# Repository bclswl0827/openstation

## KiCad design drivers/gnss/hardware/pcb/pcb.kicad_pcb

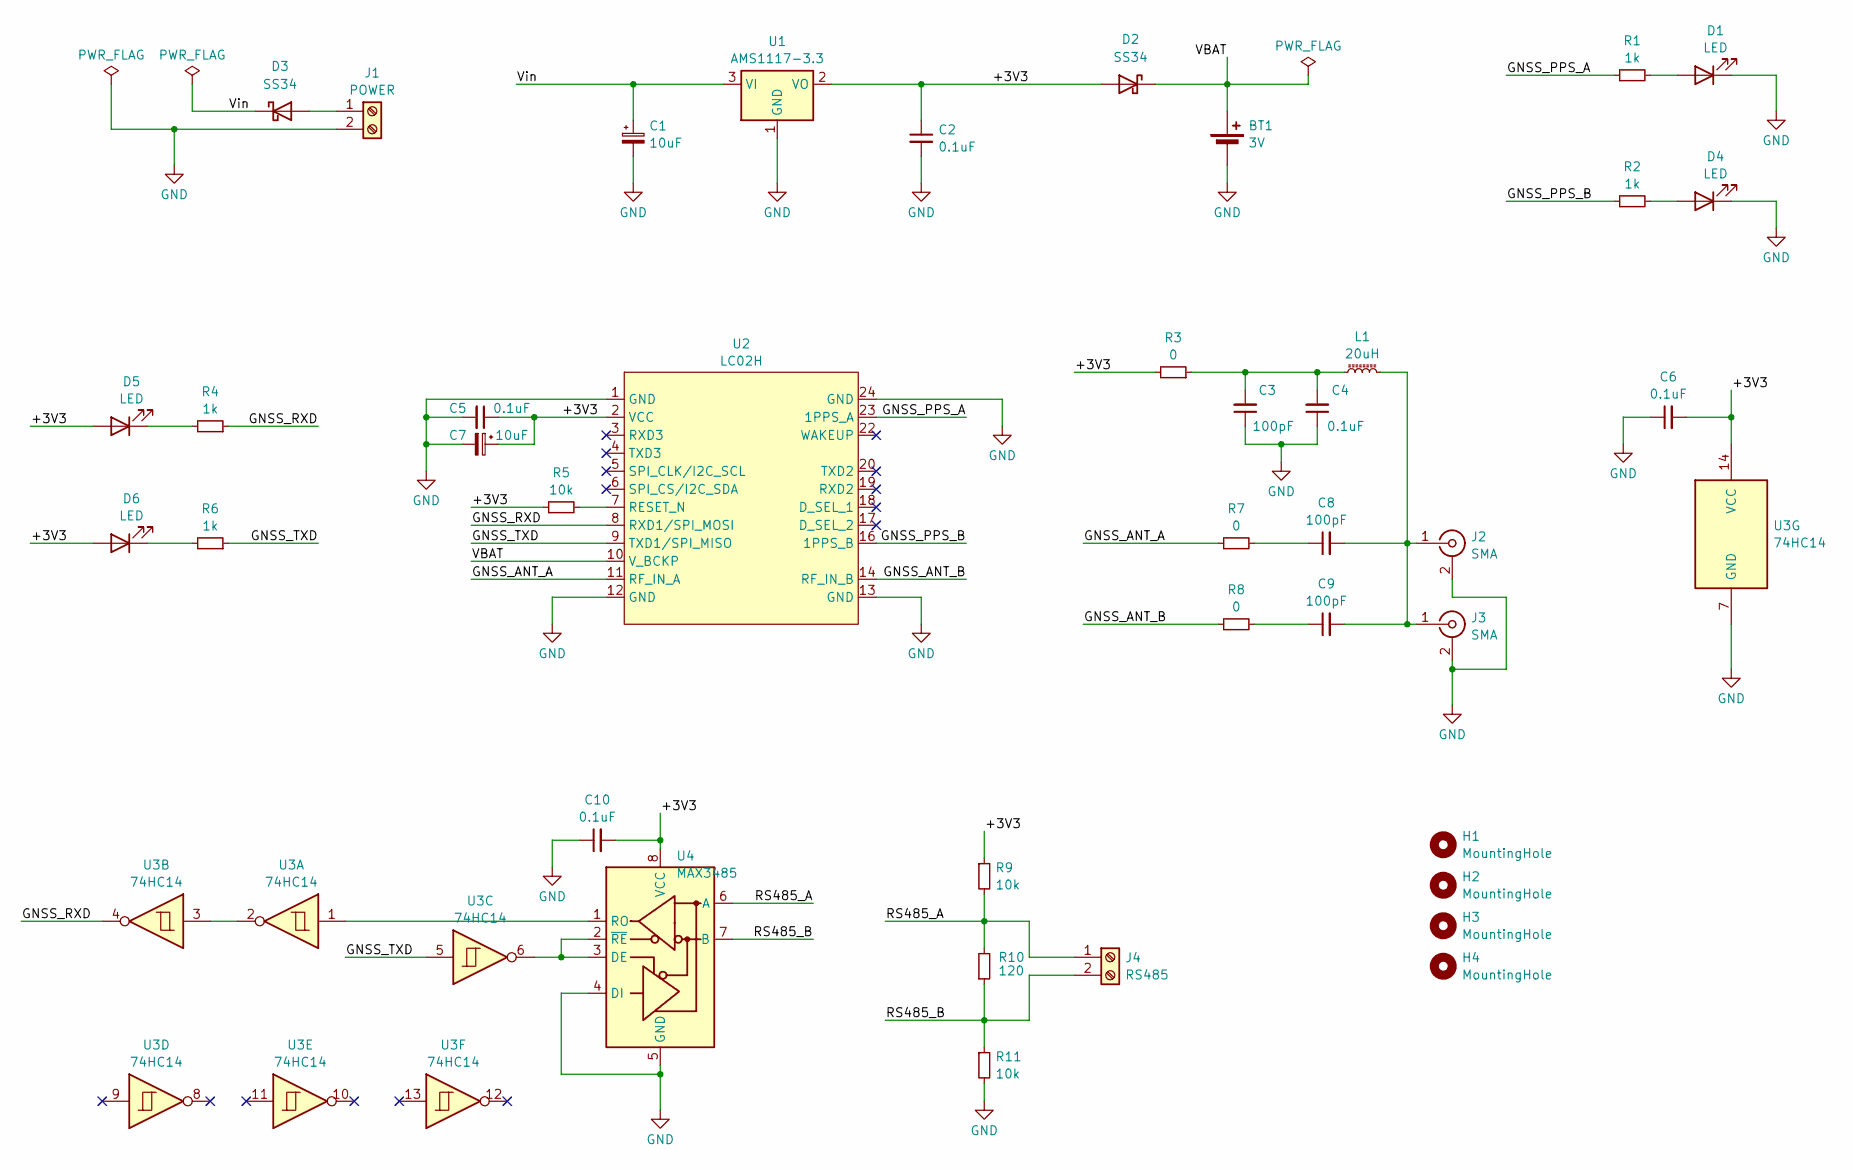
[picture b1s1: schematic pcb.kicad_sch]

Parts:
BT1: 3V; BatteryHolder_LINX_BAT-HLD-012-SMT
C1, C7: 10uF; CP_Radial_D5.0mm_P2.50mm
C2, C4, C5, C6, C10: 0.1uF; C_Disc_D3.0mm_W2.0mm_P2.50mm
C3, C8, C9: 100pF; C_Disc_D3.0mm_W2.0mm_P2.50mm
D1, D4, D5, D6: LED; LED_D3.0mm
D2, D3: SS34; D_SMA
H1, H2, H3, H4: MountingHole; MountingHole_3.2mm_M3_DIN965
J1: POWER; TerminalBlock_bornier-2_P5.08mm
J2, J3: SMA; SMA_Amphenol_901-144_Vertical
J4: RS485; TerminalBlock_bornier-2_P5.08mm
L1: 20uH; L_Radial_D7.0mm_P3.00mm
R1, R2, R4, R6: 1k; R_Axial_DIN0204_L3.6mm_D1.6mm_P7.62mm_Horizontal
R3, R7, R8: 0; R_Axial_DIN0204_L3.6mm_D1.6mm_P7.62mm_Horizontal
R5, R9, R11: 10k; R_Axial_DIN0204_L3.6mm_D1.6mm_P7.62mm_Horizontal
R10: 120; R_Axial_DIN0204_L3.6mm_D1.6mm_P7.62mm_Horizontal
U1: AMS1117-3.3; SOT-223-3_TabPin2
U2: LC02H
U3: 74HC14; SOIC-14_3.9x8.7mm_P1.27mm
U4: MAX3485; SOIC-8_3.9x4.9mm_P1.27mm

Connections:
/+3V3: C2.1, C5.1, C6.2, C7.1, C10.2, D2.2 (A), D5.2 (A), D6.2 (A), R3.2, R5.1, R9.1, U1.2 (VO), U2.2 (VCC), U3.14 (VCC), U4.8 (VCC)
/GNSS_ANT_A: R7.1, U2.11 (RF_IN_A)
/GNSS_ANT_B: R8.1, U2.14 (RF_IN_B)
/GNSS_PPS_A: R1.1, U2.23 (1PPS_A)
/GNSS_PPS_B: R2.1, U2.16 (1PPS_B)
/GNSS_RXD: R4.1, U2.8 (RXD1/SPI_MOSI), U3.4
/GNSS_TXD: R6.1, U2.9 (TXD1/SPI_MISO), U3.5
/RS485_A: J4.1, R9.2, R10.2, U4.6 (A)
/RS485_B: J4.2, R10.1, R11.1, U4.7 (B)
/VBAT: BT1.1 (+), D2.1 (K), U2.10 (V_BCKP)
/Vin: C1.1, D3.1 (K), U1.3 (VI)
GND: BT1.2 (-), C1.2, C2.2, C3.1, C4.1, C5.2, C6.1, C7.2, C10.1, D1.1 (K), D4.1 (K), J1.2, J2.2 (Ext), J3.2 (Ext), R11.2, U1.1 (GND), U2.1 (GND), U2.12 (GND), U2.13 (GND), U2.24 (GND), U3.7 (GND), U4.4 (DI), U4.5 (GND)
unnamed: C3.2, C4.2, L1.1, R3.1
unnamed: C8.1, R7.2
unnamed: C9.1, R8.2
unnamed: D1.2 (A), R1.2
unnamed: D3.2 (A), J1.1
unnamed: D4.2 (A), R2.2
unnamed: D5.1 (K), R4.2
unnamed: D6.1 (K), R6.2
unnamed: C8.2, C9.2, J2.1 (In), J3.1 (In), L1.2
unnamed: R5.2, U2.7 (RESET_N)
unnamed: U3.2, U3.3
unnamed: U3.6, U4.2 (~RE), U4.3 (DE)
unnamed: U3.1, U4.1 (RO)

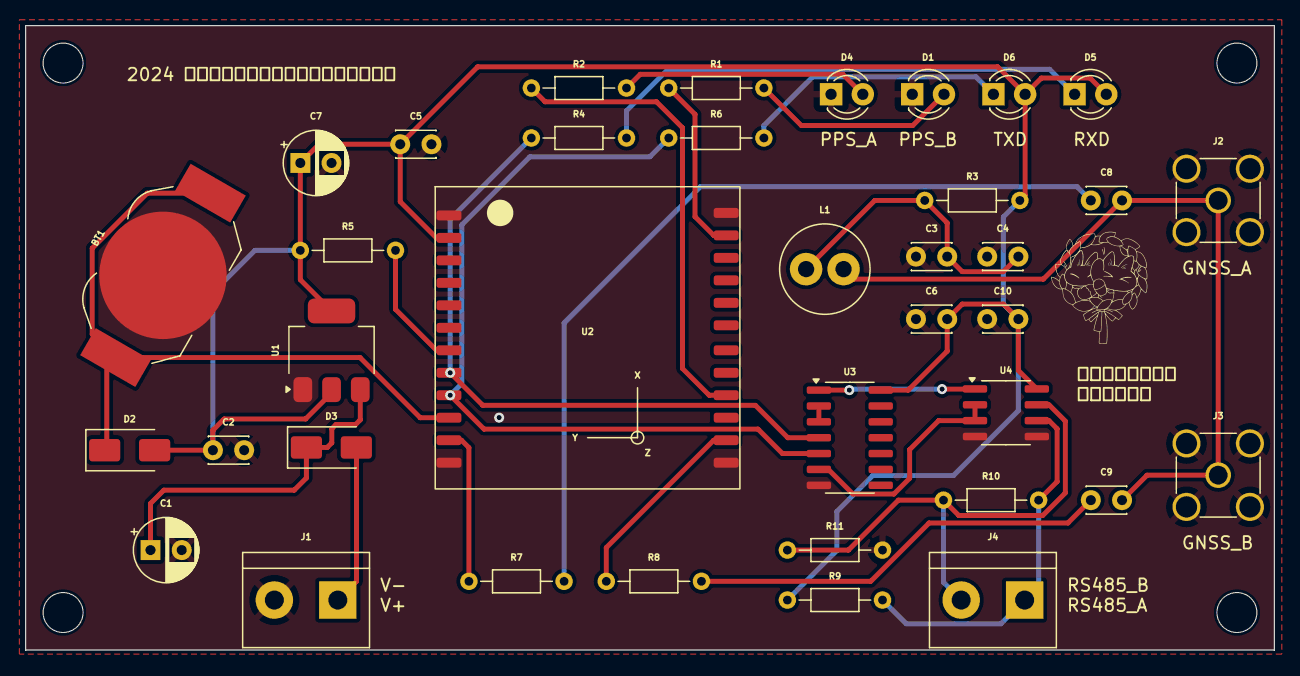
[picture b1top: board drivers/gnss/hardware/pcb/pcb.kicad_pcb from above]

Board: 2 copper layers, 100.0 x 50.0 mm, 41 parts (0 on the bottom side), 25 nets.

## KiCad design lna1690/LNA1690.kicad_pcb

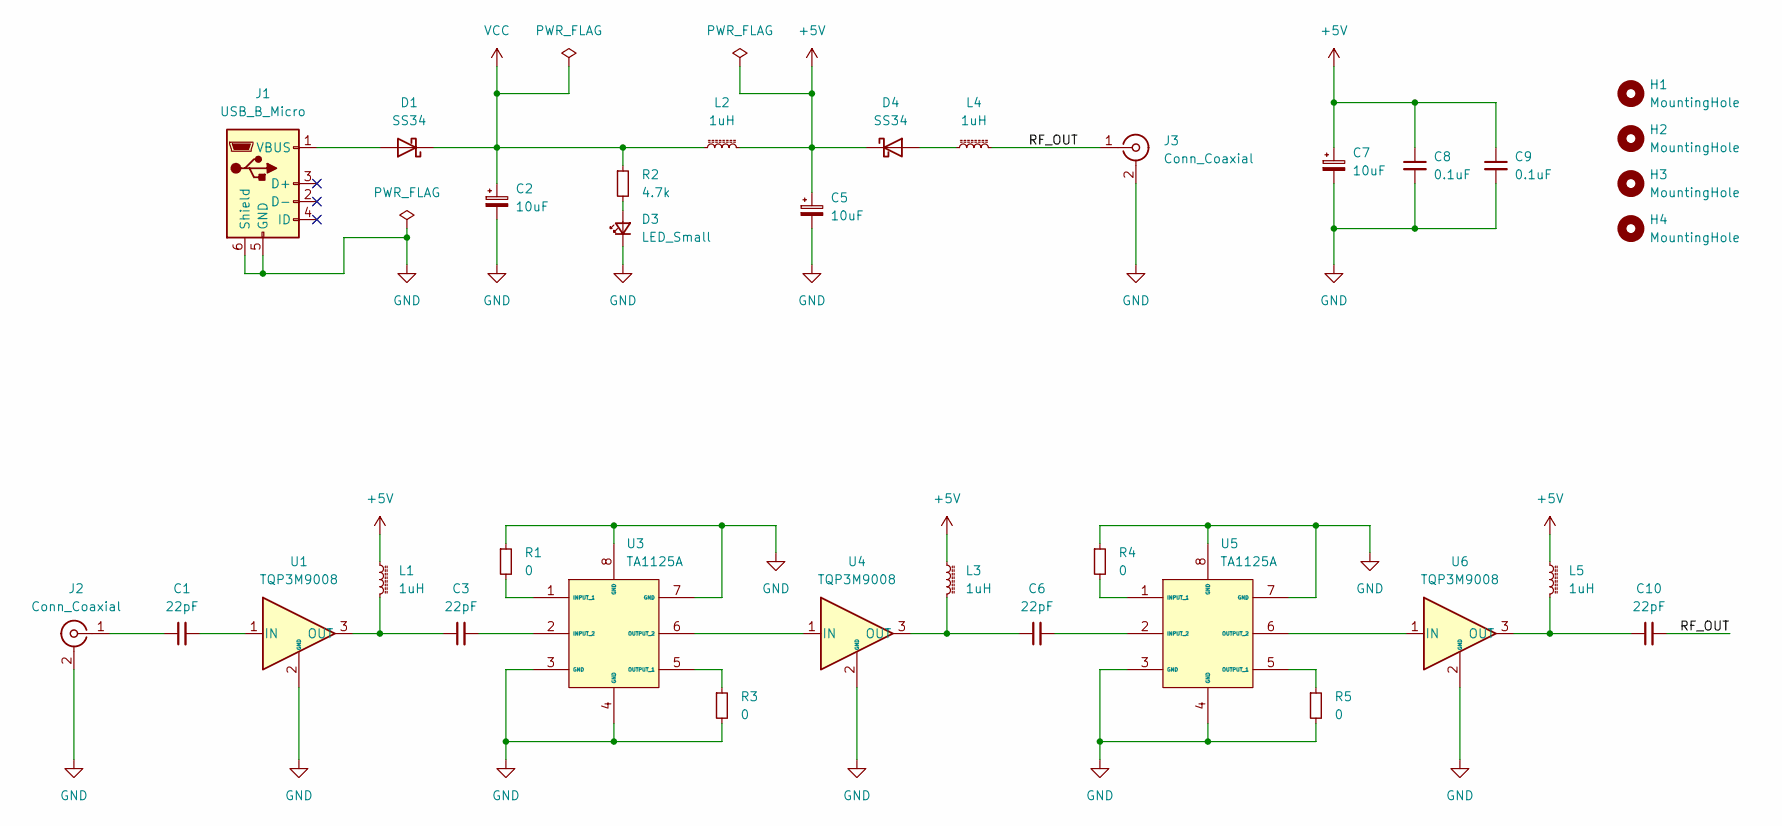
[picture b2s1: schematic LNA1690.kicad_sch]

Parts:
C1, C3, C6, C10: 22pF; C_0603_1608Metric
C2, C5, C7: 10uF; CP_EIA-3528-12_Kemet-T
C8, C9: 0.1uF; C_0603_1608Metric
D1, D4: SS34; D_SMA
D3: LED_Small; LED_0603_1608Metric
H1, H2, H3, H4: MountingHole; MountingHole_3.2mm_M3
J1: USB_B_Micro; USB_Micro-B_Amphenol_10103594-0001LF_Horizontal
J2, J3: Conn_Coaxial; SMA_Amphenol_901-144_Vertical
L1, L2, L3, L4, L5: 1uH; L_0603_1608Metric
R1, R3, R4, R5: 0; R_0603_1608Metric
R2: 4.7k; R_0603_1608Metric
U1, U4, U6: TQP3M9008; SOT-89-3
U3, U5: TA1125A; Filter_SAW-8_3.8x3.8mm

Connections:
+5V: C5.1, C7.1, C8.1, C9.1, D4.1 (K), L1.1, L2.2, L3.1, L5.1
/RF_OUT: C10.2, J3.1 (In), L4.2
GND: C2.2, C5.2, C7.2, C8.2, C9.2, D3.1 (K), J1.5 (GND), J1.6 (Shield), J2.2 (Ext), J3.2 (Ext), R1.1, R3.2, R4.1, R5.2, U1.2 (GND), U3.3 (GND), U3.4 (GND), U3.7 (GND), U3.8 (GND), U4.2 (GND), U5.3 (GND), U5.4 (GND), U5.7 (GND), U5.8 (GND), U6.2 (GND)
unnamed: D1.2 (A), J1.1 (VBUS)
unnamed: D3.2 (A), R2.2
unnamed: D4.2 (A), L4.1
unnamed: C1.1, J2.1 (In)
unnamed: C1.2, U1.1 (IN)
unnamed: C3.1, L1.2, U1.3 (OUT)
unnamed: R1.2, U3.1 (INPUT_1)
unnamed: C3.2, U3.2 (INPUT_2)
unnamed: R3.1, U3.5 (OUTPUT_1)
unnamed: U3.6 (OUTPUT_2), U4.1 (IN)
unnamed: C6.1, L3.2, U4.3 (OUT)
unnamed: R4.2, U5.1 (INPUT_1)
unnamed: C6.2, U5.2 (INPUT_2)
unnamed: R5.1, U5.5 (OUTPUT_1)
unnamed: U5.6 (OUTPUT_2), U6.1 (IN)
unnamed: C10.1, L5.2, U6.3 (OUT)
VCC: C2.1, D1.1 (K), L2.1, R2.1

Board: 2 copper layers, 34 parts (0 on the bottom side), 20 nets, no tracks yet.

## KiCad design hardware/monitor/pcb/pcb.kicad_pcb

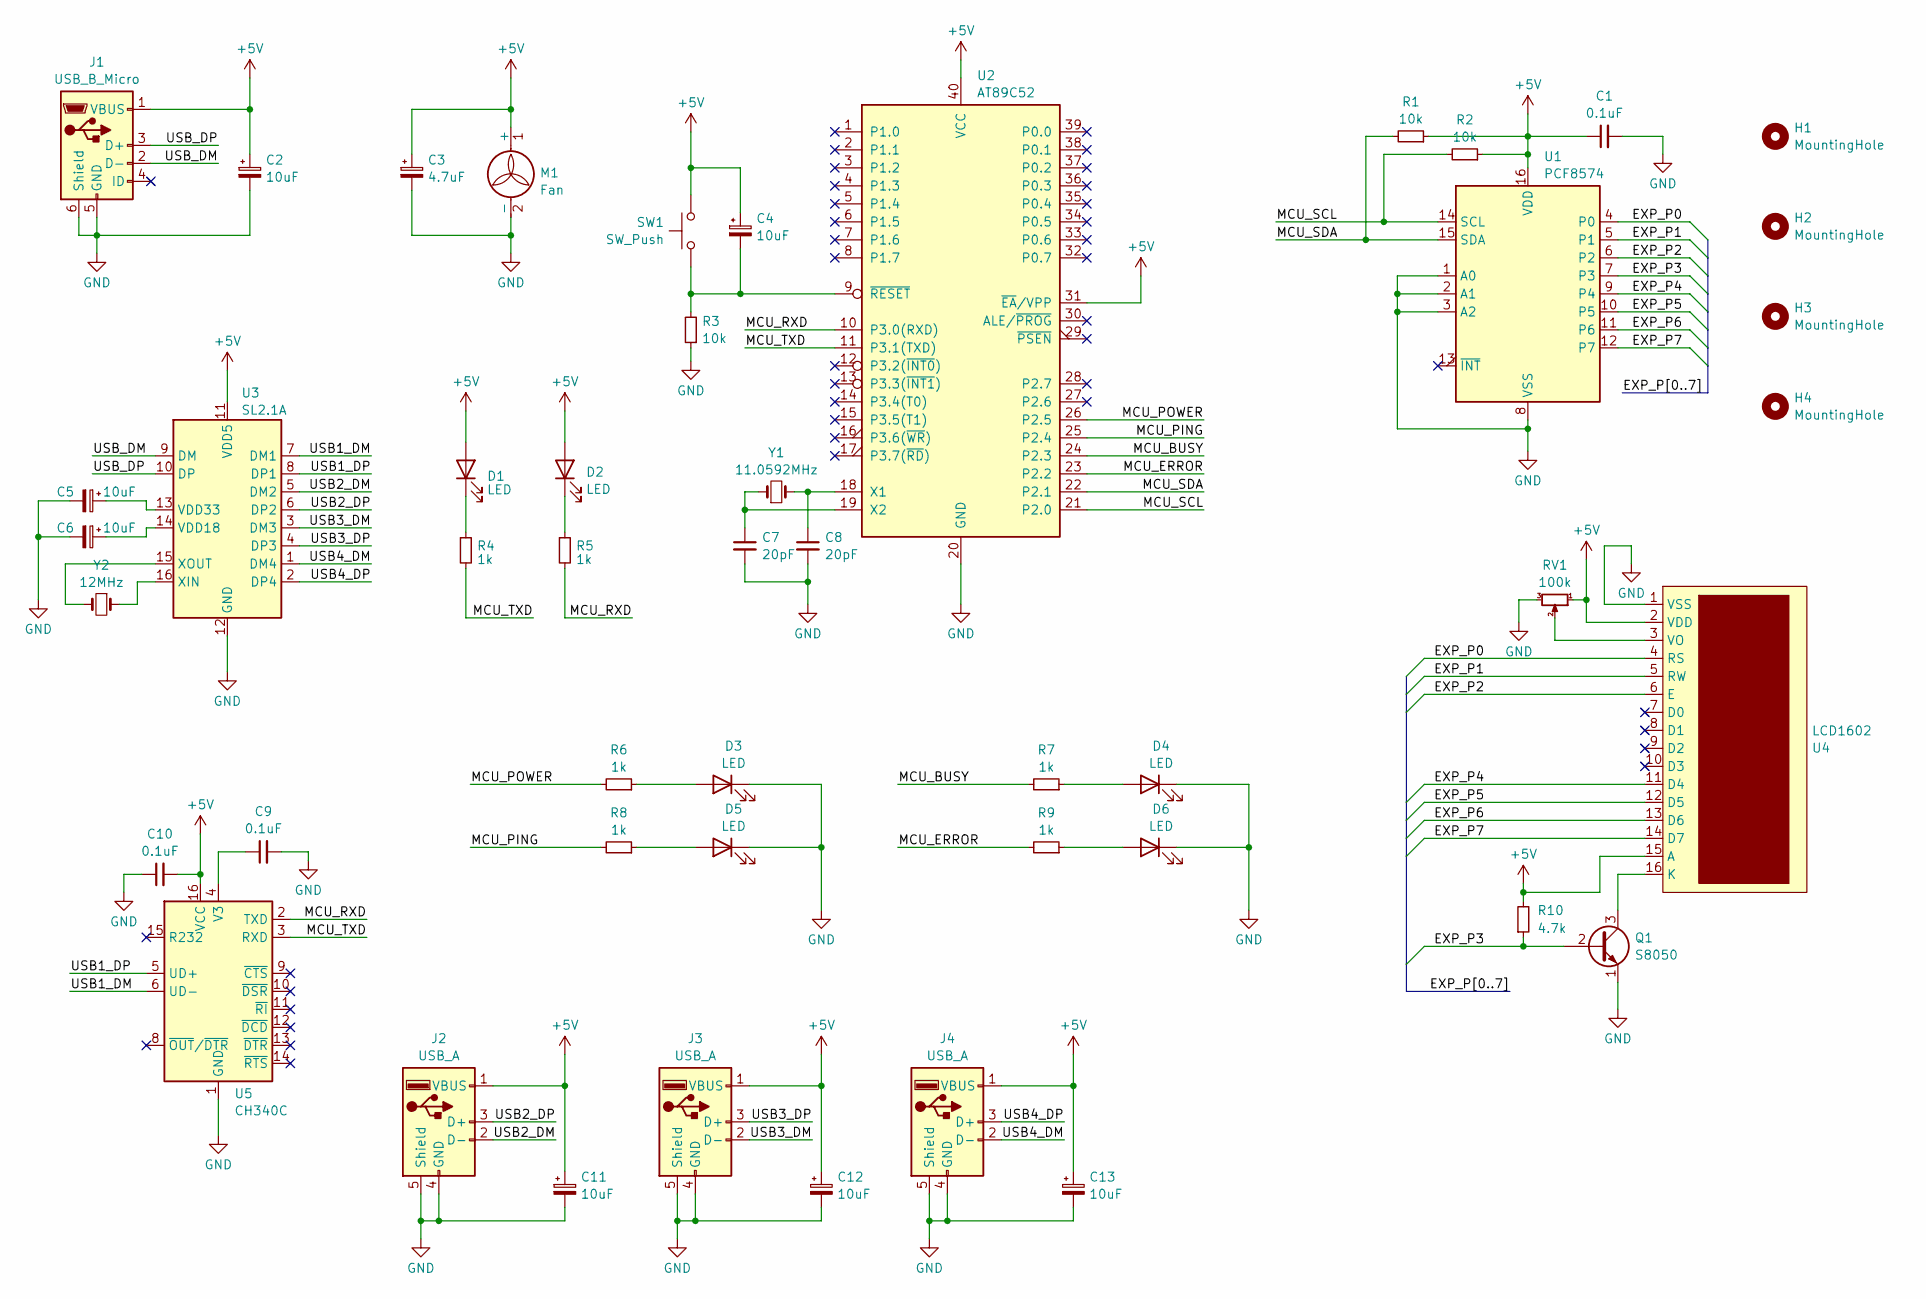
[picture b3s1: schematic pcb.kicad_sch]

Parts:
C1, C9, C10: 0.1uF; C_Disc_D3.0mm_W2.0mm_P2.50mm
C2, C4, C5, C6, C11, C12, C13: 10uF; CP_Radial_D5.0mm_P2.50mm
C3: 4.7uF; CP_Radial_D5.0mm_P2.50mm
C7, C8: 20pF; C_Disc_D3.0mm_W2.0mm_P2.50mm
D1, D2, D3, D4, D5, D6: LED; LED_D3.0mm
H1, H2, H3, H4: MountingHole; MountingHole_3.2mm_M3
J1: USB_B_Micro; USB_Micro-B_Molex-105017-0001
J2, J3, J4: USB_A; USB_A_CONNFLY_DS1095-WNR0
M1: Fan; Fan_30x30mm
Q1: S8050; TO-92_Inline
R1, R2, R3: 10k; R_Axial_DIN0204_L3.6mm_D1.6mm_P7.62mm_Horizontal
R4, R5, R6, R7, R8, R9: 1k; R_Axial_DIN0204_L3.6mm_D1.6mm_P7.62mm_Horizontal
R10: 4.7k; R_Axial_DIN0204_L3.6mm_D1.6mm_P7.62mm_Horizontal
RV1: 100k; Potentiometer_Bourns_3296W_Vertical
SW1: SW_Push; SW_SPST_FSMSM
U1: PCF8574; SOIC-16W_7.5x10.3mm_P1.27mm
U2: AT89C52; DIP-40_W15.24mm
U3: SL2.1A; SOIC-16_3.9x9.9mm_P1.27mm
U4: LCD1602
U5: CH340C; SOIC-16_3.9x9.9mm_P1.27mm
Y1: 11.0592MHz; Crystal_HC18-U_Vertical
Y2: 12MHz; Crystal_HC18-U_Vertical

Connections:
+5V: C1.1, C2.1, C3.1, C4.1, C10.2, C11.1, C12.1, C13.1, D1.2 (A), D2.2 (A), J1.1 (VBUS), J2.1 (VBUS), J3.1 (VBUS), J4.1 (VBUS), M1.1 (+), R1.1, R2.1, R10.2, RV1.1, SW1.1, U1.16 (VDD), U2.31 (~EA/VPP), U2.40 (VCC), U3.11 (VDD5), U4.2 (VDD), U4.15 (A), U5.16 (VCC); also elsewhere on the board
/EXP_P0: U1.4 (P0), U4.4 (RS)
/EXP_P1: U1.5 (P1), U4.5 (RW)
/EXP_P2: U1.6 (P2), U4.6 (E)
/EXP_P3: Q1.2 (B), R10.1, U1.7 (P3)
/EXP_P4: U1.9 (P4), U4.11 (D4)
/EXP_P5: U1.10 (P5), U4.12 (D5)
/EXP_P6: U1.11 (P6), U4.13 (D6)
/EXP_P7: U1.12 (P7), U4.14 (D7)
/MCU_BUSY: R7.2, U2.24 (P2.3)
/MCU_ERROR: R9.2, U2.23 (P2.2)
/MCU_PING: R8.2, U2.25 (P2.4)
/MCU_POWER: R6.2, U2.26 (P2.5)
/MCU_RXD: R5.2, U2.10 (P3.0(RXD)), U5.2 (TXD); also elsewhere on the board
/MCU_SCL: R2.2, U1.14 (SCL), U2.21 (P2.0)
/MCU_SDA: R1.2, U1.15 (SDA), U2.22 (P2.1)
/MCU_TXD: R4.2, U2.11 (P3.1(TXD)), U5.3 (RXD); also elsewhere on the board
/USB1_DM: U3.7 (DM1), U5.6 (UD-); also elsewhere on the board
/USB1_DP: U3.8 (DP1), U5.5 (UD+); also elsewhere on the board
/USB2_DM: J2.2 (D-), U3.5 (DM2)
/USB2_DP: J2.3 (D+), U3.6 (DP2)
/USB3_DM: J3.2 (D-), U3.3 (DM3)
/USB3_DP: J3.3 (D+), U3.4 (DP3)
/USB4_DM: J4.2 (D-), U3.1 (DM4)
/USB4_DP: J4.3 (D+), U3.2 (DP4)
/USB_DM: J1.2 (D-), U3.9 (DM)
/USB_DP: J1.3 (D+), U3.10 (DP)
GND: C1.2, C2.2, C3.2, C5.2, C6.2, C7.2, C8.2, C9.2, C10.1, C11.2, C12.2, C13.2, D3.1 (K), D4.1 (K), D5.1 (K), D6.1 (K), J1.5 (GND), J1.6 (Shield), J2.4 (GND), J2.5 (Shield), J3.4 (GND), J3.5 (Shield), J4.4 (GND), J4.5 (Shield), M1.2 (-), Q1.1 (E), R3.1, RV1.3, U1.1 (A0), U1.2 (A1), U1.3 (A2), U1.8 (VSS), U2.20 (GND), U3.12 (GND), U4.1 (VSS), U5.1 (GND); also elsewhere on the board
unnamed: C9.1, U5.4 (V3)
unnamed: D1.1 (K), R4.1
unnamed: D2.1 (K), R5.1
unnamed: D3.2 (A), R6.1
unnamed: D4.2 (A), R7.1
unnamed: D5.2 (A), R8.1
unnamed: D6.2 (A), R9.1
unnamed: Q1.3 (C), U4.16 (K)
unnamed: C8.1, U2.18 (X1), Y1.2
unnamed: C7.1, U2.19 (X2), Y1.1
unnamed: C4.2, R3.2, SW1.2, U2.9 (~RESET)
unnamed: C6.1, U3.14 (VDD18)
unnamed: C5.1, U3.13 (VDD33)
unnamed: U3.16 (XIN), Y2.1
unnamed: U3.15 (XOUT), Y2.2
unnamed: RV1.2, U4.3 (VO)

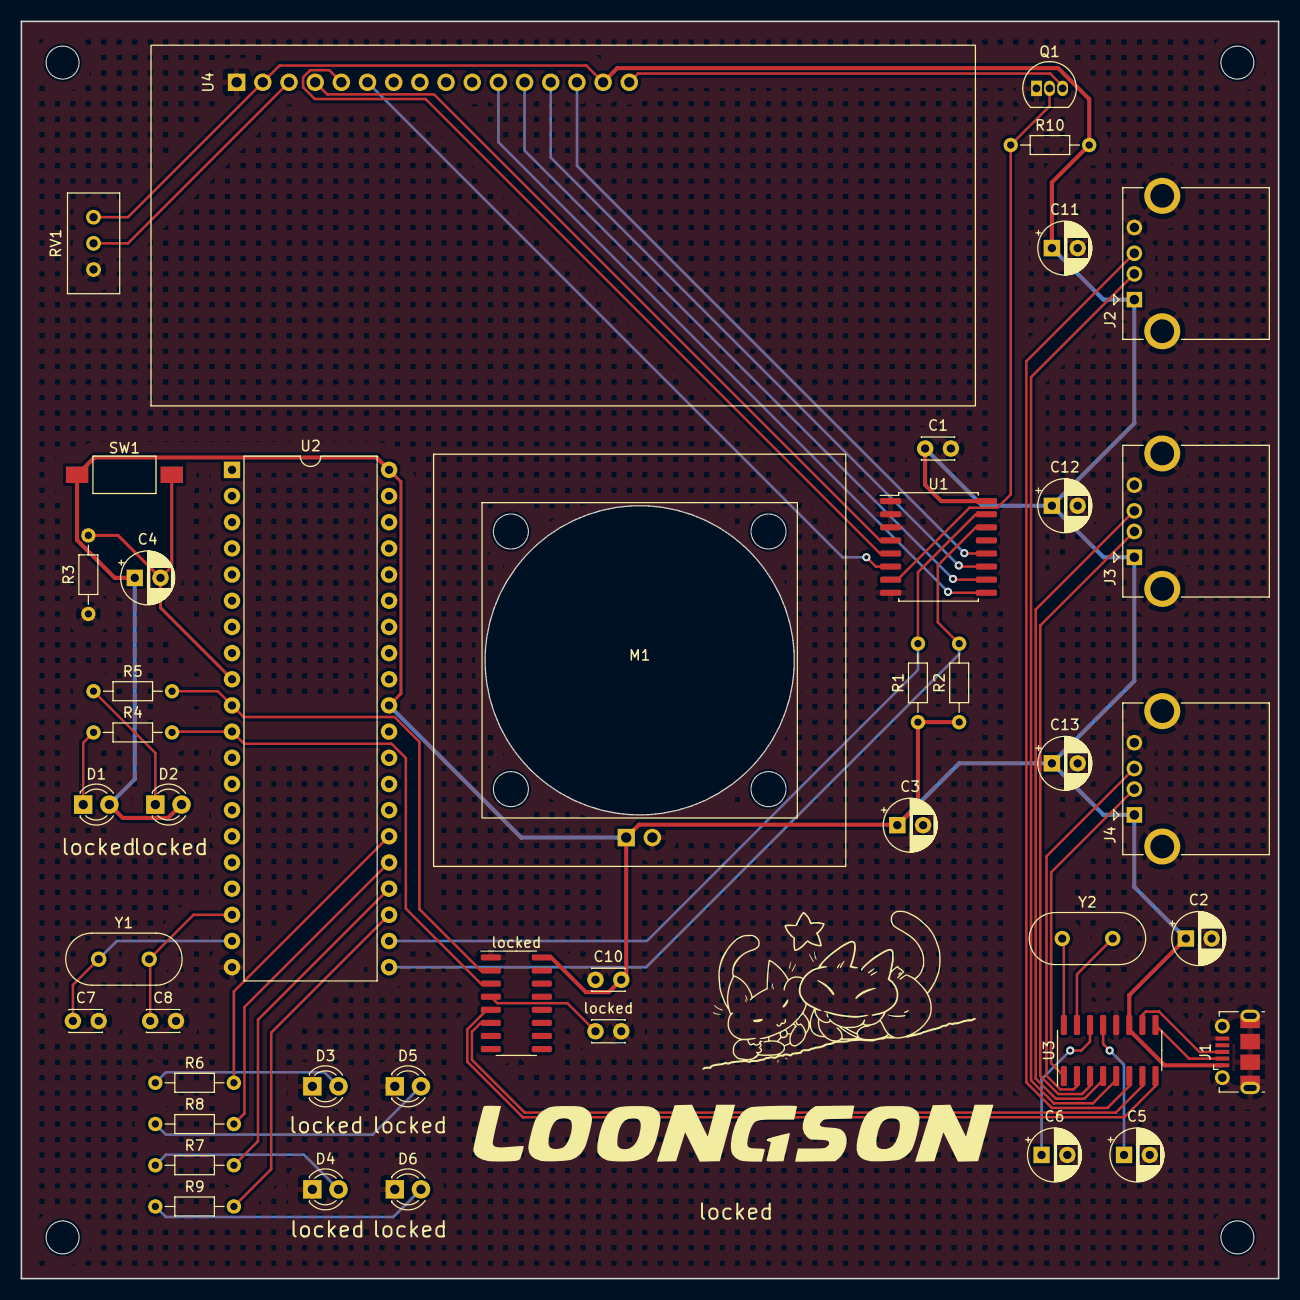
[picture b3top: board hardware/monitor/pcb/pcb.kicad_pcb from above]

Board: 2 copper layers, 122.0 x 122.0 mm, 48 parts (0 on the bottom side), 44 nets.

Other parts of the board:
locked: 0.1uF; C_Disc_D3.0mm_W2.0mm_P2.50mm
locked#2: CH340C; SOIC-16_3.9x9.9mm_P1.27mm

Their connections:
+5V: locked#2.16 (VCC); also elsewhere on the board
/MCU_RXD: locked#2.2 (TXD); also elsewhere on the board
/MCU_TXD: locked#2.3 (RXD); also elsewhere on the board
/USB1_DM: locked#2.6 (UD-); also elsewhere on the board
/USB1_DP: locked#2.5 (UD+); also elsewhere on the board
GND: locked.2, locked#2.1 (GND); also elsewhere on the board
unnamed: locked.1, locked#2.4 (V3)

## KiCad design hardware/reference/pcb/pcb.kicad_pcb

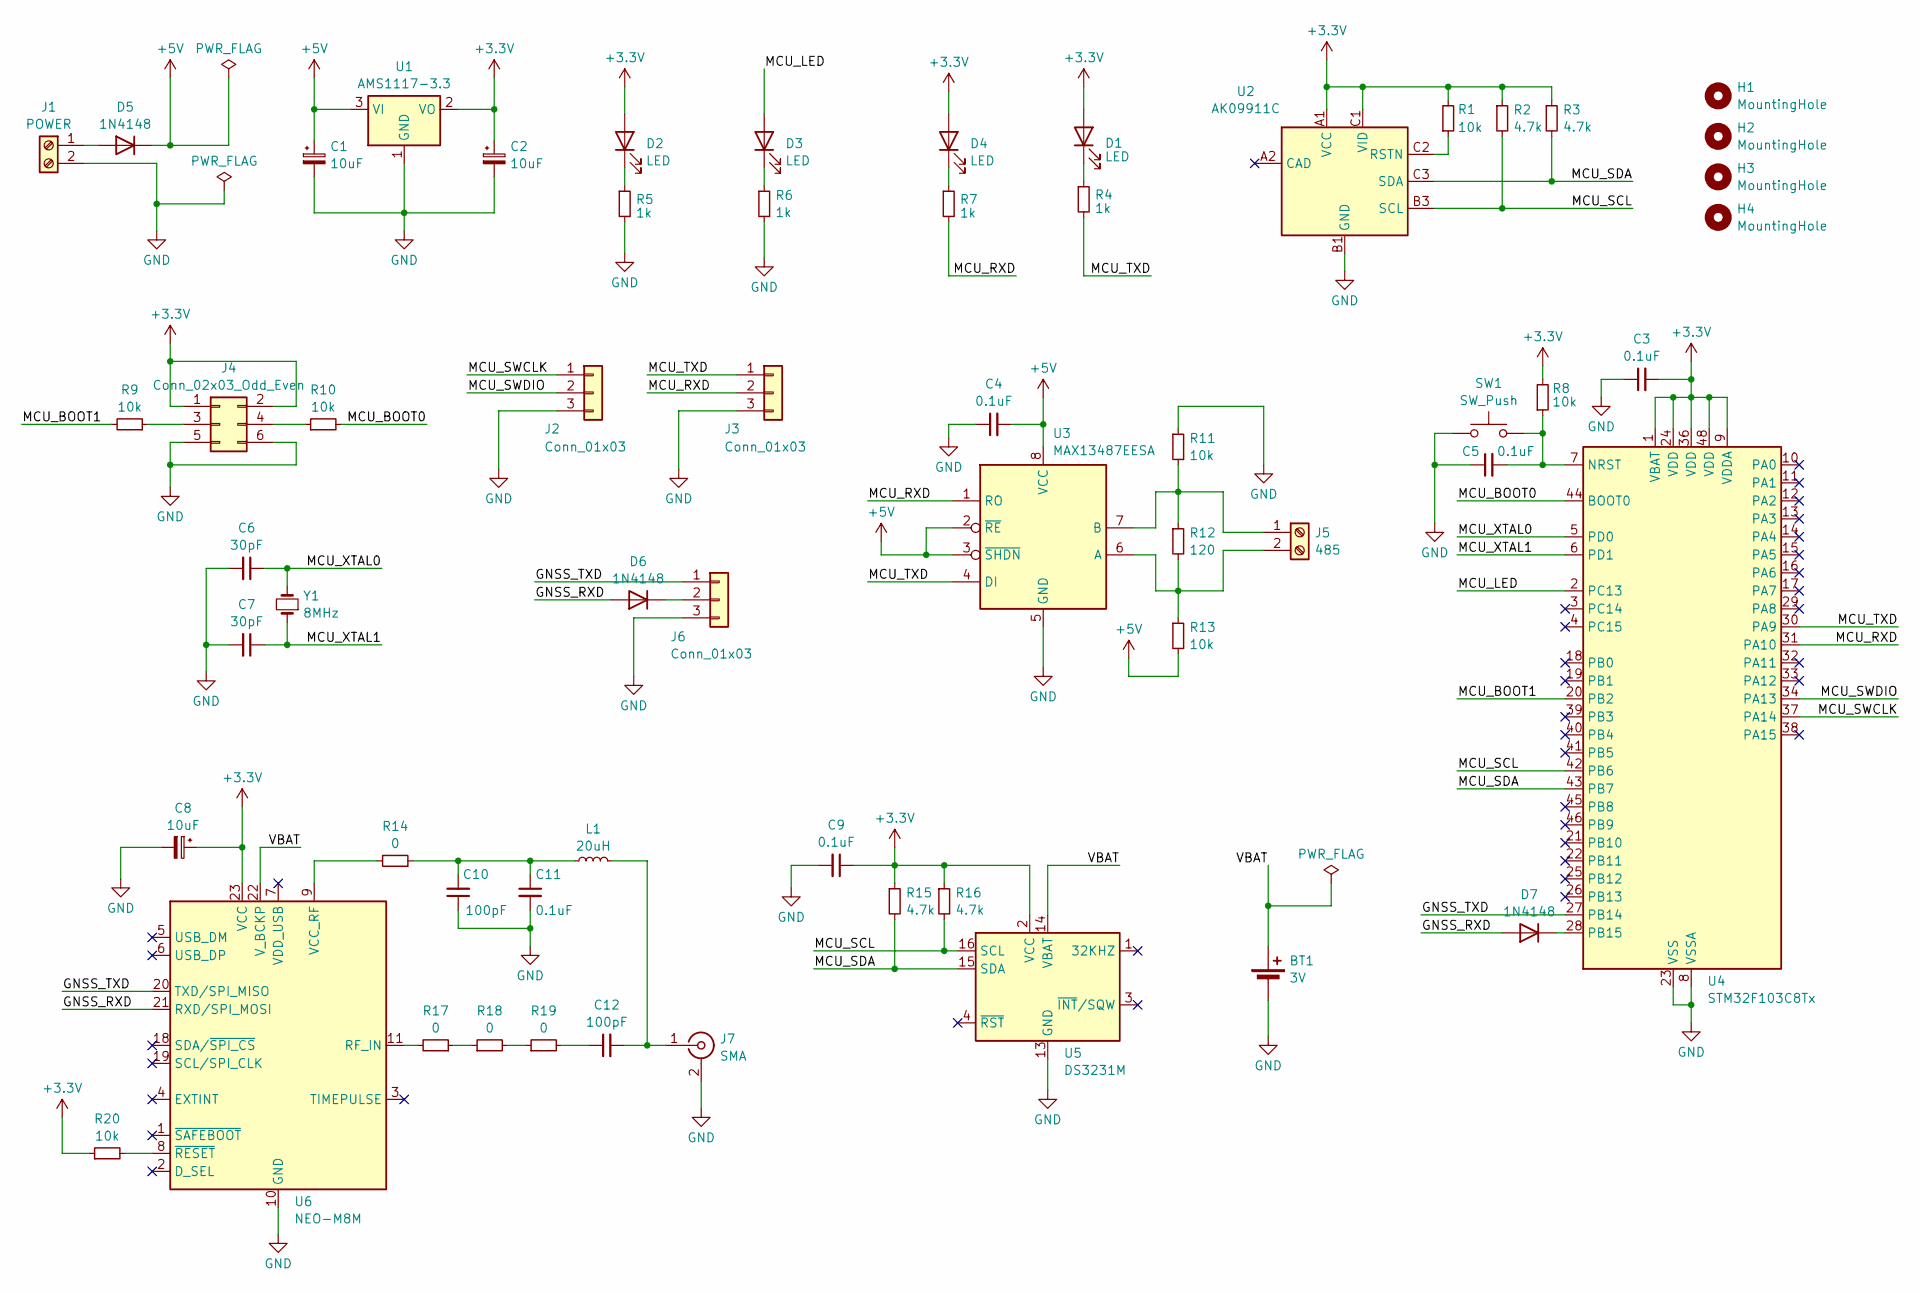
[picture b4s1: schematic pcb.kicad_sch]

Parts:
BT1: 3V; BatteryHolder_LINX_BAT-HLD-012-SMT
C1, C2, C8: 10uF; CP_Radial_D5.0mm_P2.50mm
C3, C4, C5, C9, C11: 0.1uF; C_Disc_D3.0mm_W2.0mm_P2.50mm
C6, C7: 30pF; C_Disc_D3.0mm_W2.0mm_P2.50mm
C10, C12: 100pF; C_Disc_D3.0mm_W2.0mm_P2.50mm
D1, D2, D3, D4: LED; LED_D3.0mm
D5, D6, D7: 1N4148; D_DO-35_SOD27_P7.62mm_Horizontal
H1, H2, H3, H4: MountingHole; MountingHole_3.2mm_M3_DIN965
J1: POWER; TerminalBlock_bornier-2_P5.08mm
J2, J3, J6: Conn_01x03; PinHeader_1x03_P2.54mm_Vertical
J4: Conn_02x03_Odd_Even; PinHeader_2x03_P2.54mm_Vertical
J5: 485; TerminalBlock_bornier-2_P5.08mm
J7: SMA; SMA_Amphenol_901-144_Vertical
L1: 20uH; L_Radial_D7.0mm_P3.00mm
R1, R8, R9, R10, R11, R13, R20: 10k; R_Axial_DIN0204_L3.6mm_D1.6mm_P7.62mm_Horizontal
R2, R3, R15, R16: 4.7k; R_Axial_DIN0204_L3.6mm_D1.6mm_P7.62mm_Horizontal
R4, R5, R6, R7: 1k; R_Axial_DIN0204_L3.6mm_D1.6mm_P7.62mm_Horizontal
R12: 120; R_Axial_DIN0204_L3.6mm_D1.6mm_P7.62mm_Horizontal
R14, R17, R18, R19: 0; R_Axial_DIN0204_L3.6mm_D1.6mm_P7.62mm_Horizontal
SW1: SW_Push; SW_SPST_FSMSM
U1: AMS1117-3.3; SOT-223-3_TabPin2
U2: AK09911C
U3: MAX13487EESA; SOP-8_3.9x4.9mm_P1.27mm
U4: STM32F103C8Tx; LQFP-48_7x7mm_P0.5mm
U5: DS3231M; SOIC-16W_7.5x10.3mm_P1.27mm
U6: NEO-M8M; ublox_NEO
Y1: 8MHz; Crystal_HC18-U_Vertical

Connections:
+3.3V: C2.1, C3.2, C8.1, C9.1, D1.2 (A), D2.2 (A), D4.2 (A), J4.1, J4.2, R1.2, R2.1, R3.1, R8.2, R15.1, R16.1, R20.1, U1.2 (VO), U2.A1 (VCC), U2.C1 (VID), U4.1 (VBAT), U4.9 (VDDA), U4.24 (VDD), U4.36 (VDD), U4.48 (VDD), U5.2 (VCC), U6.23 (VCC)
+5V: C1.1, C4.2, D5.1 (K), R13.2, U1.3 (VI), U3.2 (~RE), U3.3 (~SHDN), U3.8 (VCC); also elsewhere on the board
/GNSS_RXD: D6.2 (A), D7.2 (A), U6.21 (RXD/SPI_MOSI)
/GNSS_TXD: J6.1, U4.27 (PB14), U6.20 (TXD/SPI_MISO)
/MCU_BOOT0: R10.2, U4.44 (BOOT0)
/MCU_BOOT1: R9.2, U4.20 (PB2)
/MCU_LED: D3.2 (A), U4.2 (PC13)
/MCU_RXD: J3.2, R7.2, U3.1 (RO), U4.31 (PA10); also elsewhere on the board
/MCU_SCL: R2.2, R16.2, U2.B3 (SCL), U4.42 (PB6), U5.16 (SCL)
/MCU_SDA: R3.2, R15.2, U2.C3 (SDA), U4.43 (PB7), U5.15 (SDA)
/MCU_SWCLK: J2.1, U4.37 (PA14); also elsewhere on the board
/MCU_SWDIO: J2.2, U4.34 (PA13); also elsewhere on the board
/MCU_TXD: J3.1, R4.2, U3.4 (DI), U4.30 (PA9); also elsewhere on the board
/MCU_XTAL0: C6.1, U4.5 (PD0), Y1.2
/MCU_XTAL1: C7.1, U4.6 (PD1), Y1.1
/VBAT: BT1.1 (+), U5.14 (VBAT), U6.22 (V_BCKP)
GND: BT1.2 (-), C1.2, C2.2, C3.1, C4.1, C5.1, C6.2, C7.2, C8.2, C9.2, C10.1, C11.2, J1.2, J2.3, J3.3, J4.5, J4.6, J6.3, J7.2 (Ext), R5.2, R6.2, R11.1, SW1.2, U1.1 (GND), U2.B1 (GND), U3.5 (GND), U4.8 (VSSA), U4.23 (VSS), U4.35 (VSS), U4.47 (VSS), U5.5 (GND), U5.6 (GND), U5.7 (GND), U5.8 (GND), U5.9 (GND), U5.10 (GND), U5.11 (GND), U5.12 (GND), U5.13 (GND), U6.10 (GND), U6.12 (GND), U6.13 (GND), U6.24 (GND); also elsewhere on the board
unnamed: C10.2, C11.1, L1.1, R14.1
unnamed: C12.1, R19.2
unnamed: D1.1 (K), R4.1
unnamed: D2.1 (K), R5.1
unnamed: D3.1 (K), R6.1
unnamed: D4.1 (K), R7.1
unnamed: D5.2 (A), J1.1
unnamed: D6.1 (K), J6.2
unnamed: D7.1 (K), U4.28 (PB15)
unnamed: J4.3, R9.1
unnamed: J4.4, R10.1
unnamed 28: J5.1, R11.2, R12.1, U3.7 (B); also elsewhere on the board
unnamed 29: J5.2, R12.2, R13.1, U3.6 (A); also elsewhere on the board
unnamed: C12.2, J7.1 (In), L1.2
unnamed: R17.1, R18.1
unnamed: R18.2, R19.1
unnamed: R1.1, U2.C2 (RSTN)
unnamed: C5.2, R8.1, SW1.1, U4.7 (NRST)
unnamed: R17.2, U6.11 (RF_IN)
unnamed: R14.2, U6.9 (VCC_RF)
unnamed: R20.2, U6.8 (~RESET)

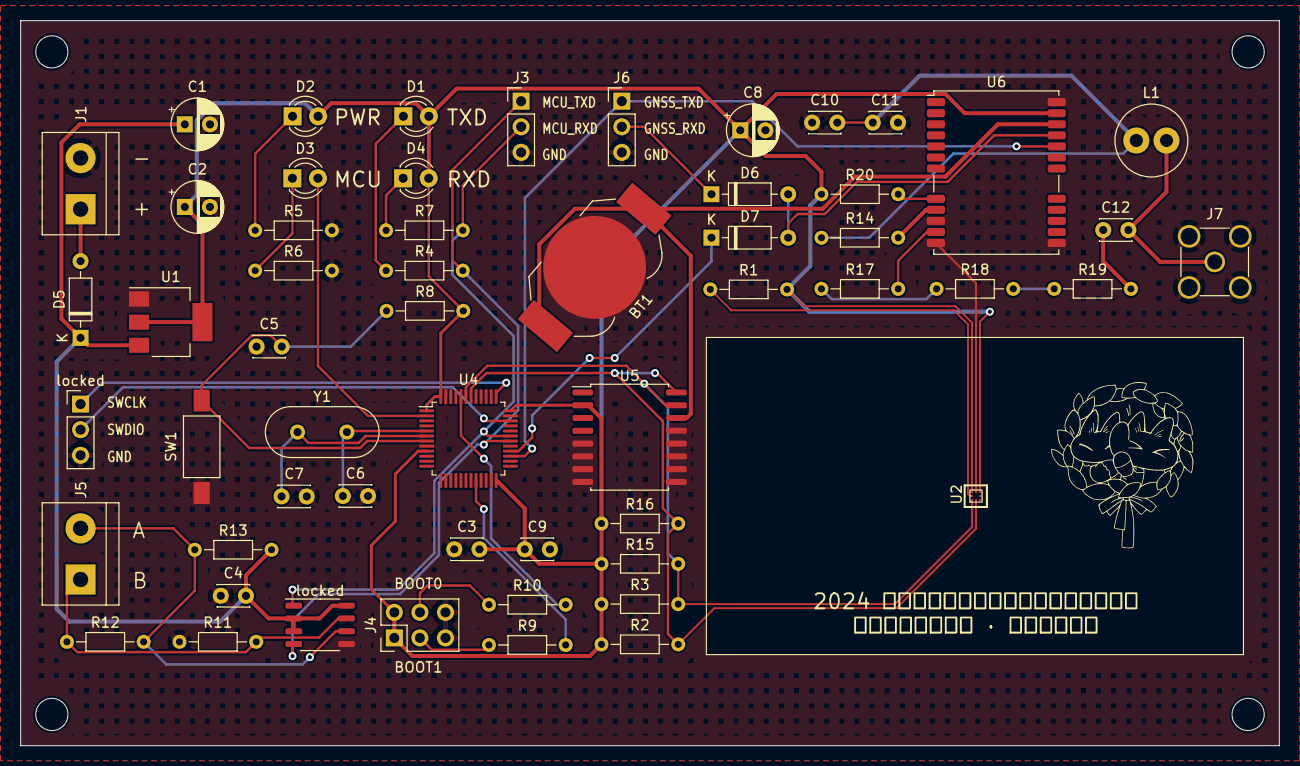
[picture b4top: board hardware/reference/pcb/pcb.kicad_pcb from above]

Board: 2 copper layers, 125.0 x 72.0 mm, 60 parts (0 on the bottom side), 38 nets.

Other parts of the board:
locked: Conn_01x03; PinHeader_1x03_P2.54mm_Vertical
locked#2: MAX13487EESA; SOP-8_3.9x4.9mm_P1.27mm

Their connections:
+5V: locked#2.2 (~RE), locked#2.3 (~SHDN), locked#2.8 (VCC); also elsewhere on the board
/MCU_RXD: locked#2.1 (RO); also elsewhere on the board
/MCU_SWCLK: locked.1; also elsewhere on the board
/MCU_SWDIO: locked.2; also elsewhere on the board
/MCU_TXD: locked#2.4 (DI); also elsewhere on the board
GND: locked.3, locked#2.5 (GND); also elsewhere on the board
unnamed 28: locked#2.7 (B); also elsewhere on the board
unnamed 29: locked#2.6 (A); also elsewhere on the board

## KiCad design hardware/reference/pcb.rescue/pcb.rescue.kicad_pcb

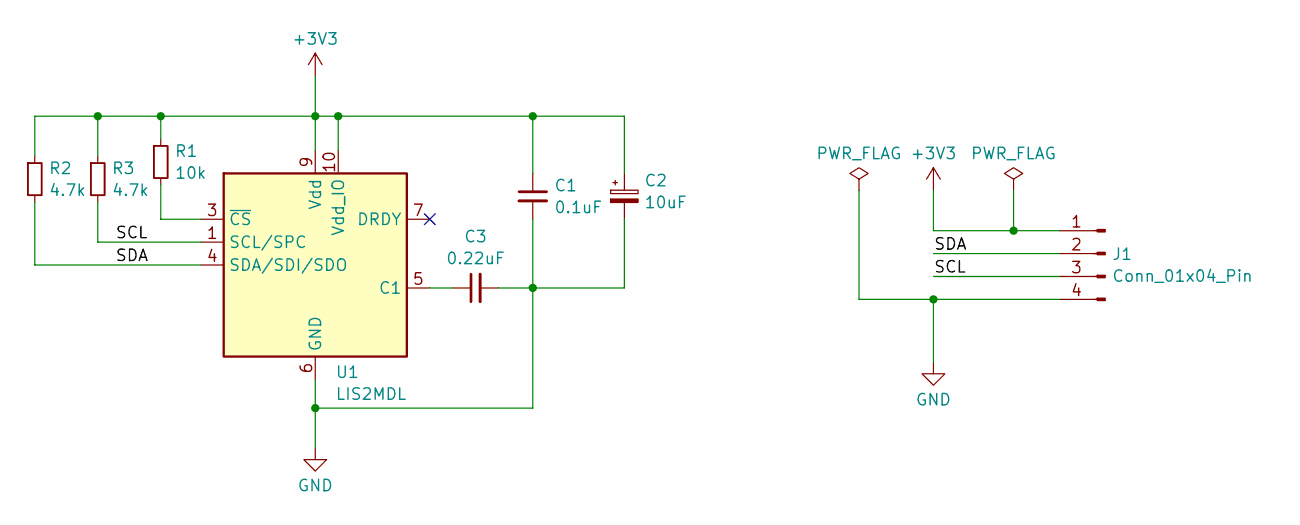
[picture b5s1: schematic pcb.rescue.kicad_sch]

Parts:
C1: 0.1uF; C_Disc_D3.0mm_W2.0mm_P2.50mm
C2: 10uF; CP_Radial_D5.0mm_P2.50mm
C3: 0.22uF; C_Disc_D3.0mm_W2.0mm_P2.50mm
J1: Conn_01x04_Pin; PinHeader_1x04_P2.54mm_Vertical
R1: 10k; R_Axial_DIN0204_L3.6mm_D1.6mm_P7.62mm_Horizontal
R2, R3: 4.7k; R_Axial_DIN0204_L3.6mm_D1.6mm_P7.62mm_Horizontal
U1: LIS2MDL; LGA-12_2x2mm_P0.5mm

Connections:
+3V3: C1.1, C2.1, J1.1, R1.1, R2.1, R3.1, U1.9 (Vdd), U1.10 (Vdd_IO)
/SCL: J1.3, R3.2, U1.1 (SCL/SPC)
/SDA: J1.2, R2.2, U1.4 (SDA/SDI/SDO)
GND: C1.2, C2.2, C3.2, J1.4, U1.6 (GND), U1.8 (GND)
unnamed: C3.1, U1.5 (C1)
unnamed: R1.2, U1.3 (~CS)

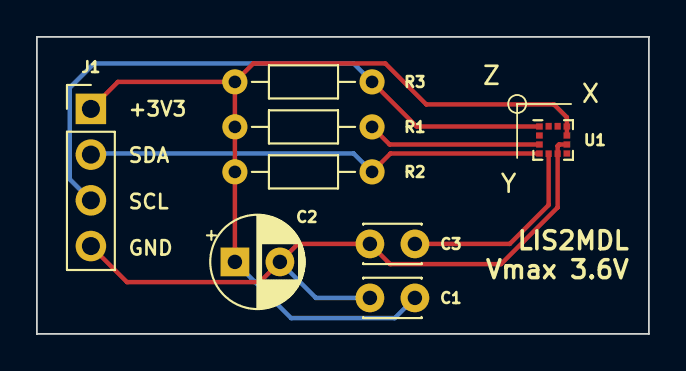
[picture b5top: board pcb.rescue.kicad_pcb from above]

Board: 2 copper layers, 34.0 x 16.5 mm, 8 parts (0 on the bottom side), 6 nets.

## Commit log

2024-04-02 Implementation of basic framework
2024-04-11 Finished hardware design of monitor module
2024-04-24 Basic implementation of frontend
2024-04-25 Updated reference board schematic & firmware
2024-04-25 Fixed an issue that may cause firmware crash
2024-04-25 Remove unused functions
2024-04-25 Remove duplicated I2C initialization function
2024-04-26 Higher GNSS read timeout threshold
2024-04-26 Combined with ADXL345
2024-04-27 Use GNSS internal RTC
2024-04-27 Avoid using global varibles
2024-04-27 Firmware stability improvements
2024-04-27 Always use RTC if GNSS is not available
2024-05-04 Implementation of TLE driver
2024-05-08 Create TLE CRUD
2024-05-08 Implemented more APIs
2024-05-09 Combine with LCD, Pan-Tilt and compass
2024-05-12 Validate config fields
2024-05-13 Add test tools
2024-05-19 Fix GNSS, use dependency injection
2024-05-20 Implemented LC02H driver
2024-05-24 With QGNSS tool
2024-06-01 Frontend implementation of home & debug
2024-06-11 Update GNSS schematic
2024-06-12 Isolate monitor device
2024-06-15 Implementation of satellite forecast and orbit preview
2024-06-16 Implemented satellite tasks related API
2024-06-17 Complete calendar view of tasks
2024-06-18 Implemented satellite tracking
2024-06-19 Implemented all basic functions
2024-06-21 Add LNA schematic & PCB design
2024-06-28 Update LNA schematic
2024-07-07 Update locales
2024-07-18 Fix Pan-Tilt error
2024-07-19 Support ethernet mode
2024-07-20 Support controlling Pan-Tilt and GNSS via TCP
2024-07-31 Remove LNA circuit
2024-07-31 Update GNSS PCB
2024-08-01 Fix some typos
2024-08-01 Stop goroutines correctly
2024-08-01 Make transport driver thread-safe
2024-08-01 Gracefully exit from readerDaemon
2024-08-07 Update Makefile
2024-12-22 fix: Fixed some typo in translations
